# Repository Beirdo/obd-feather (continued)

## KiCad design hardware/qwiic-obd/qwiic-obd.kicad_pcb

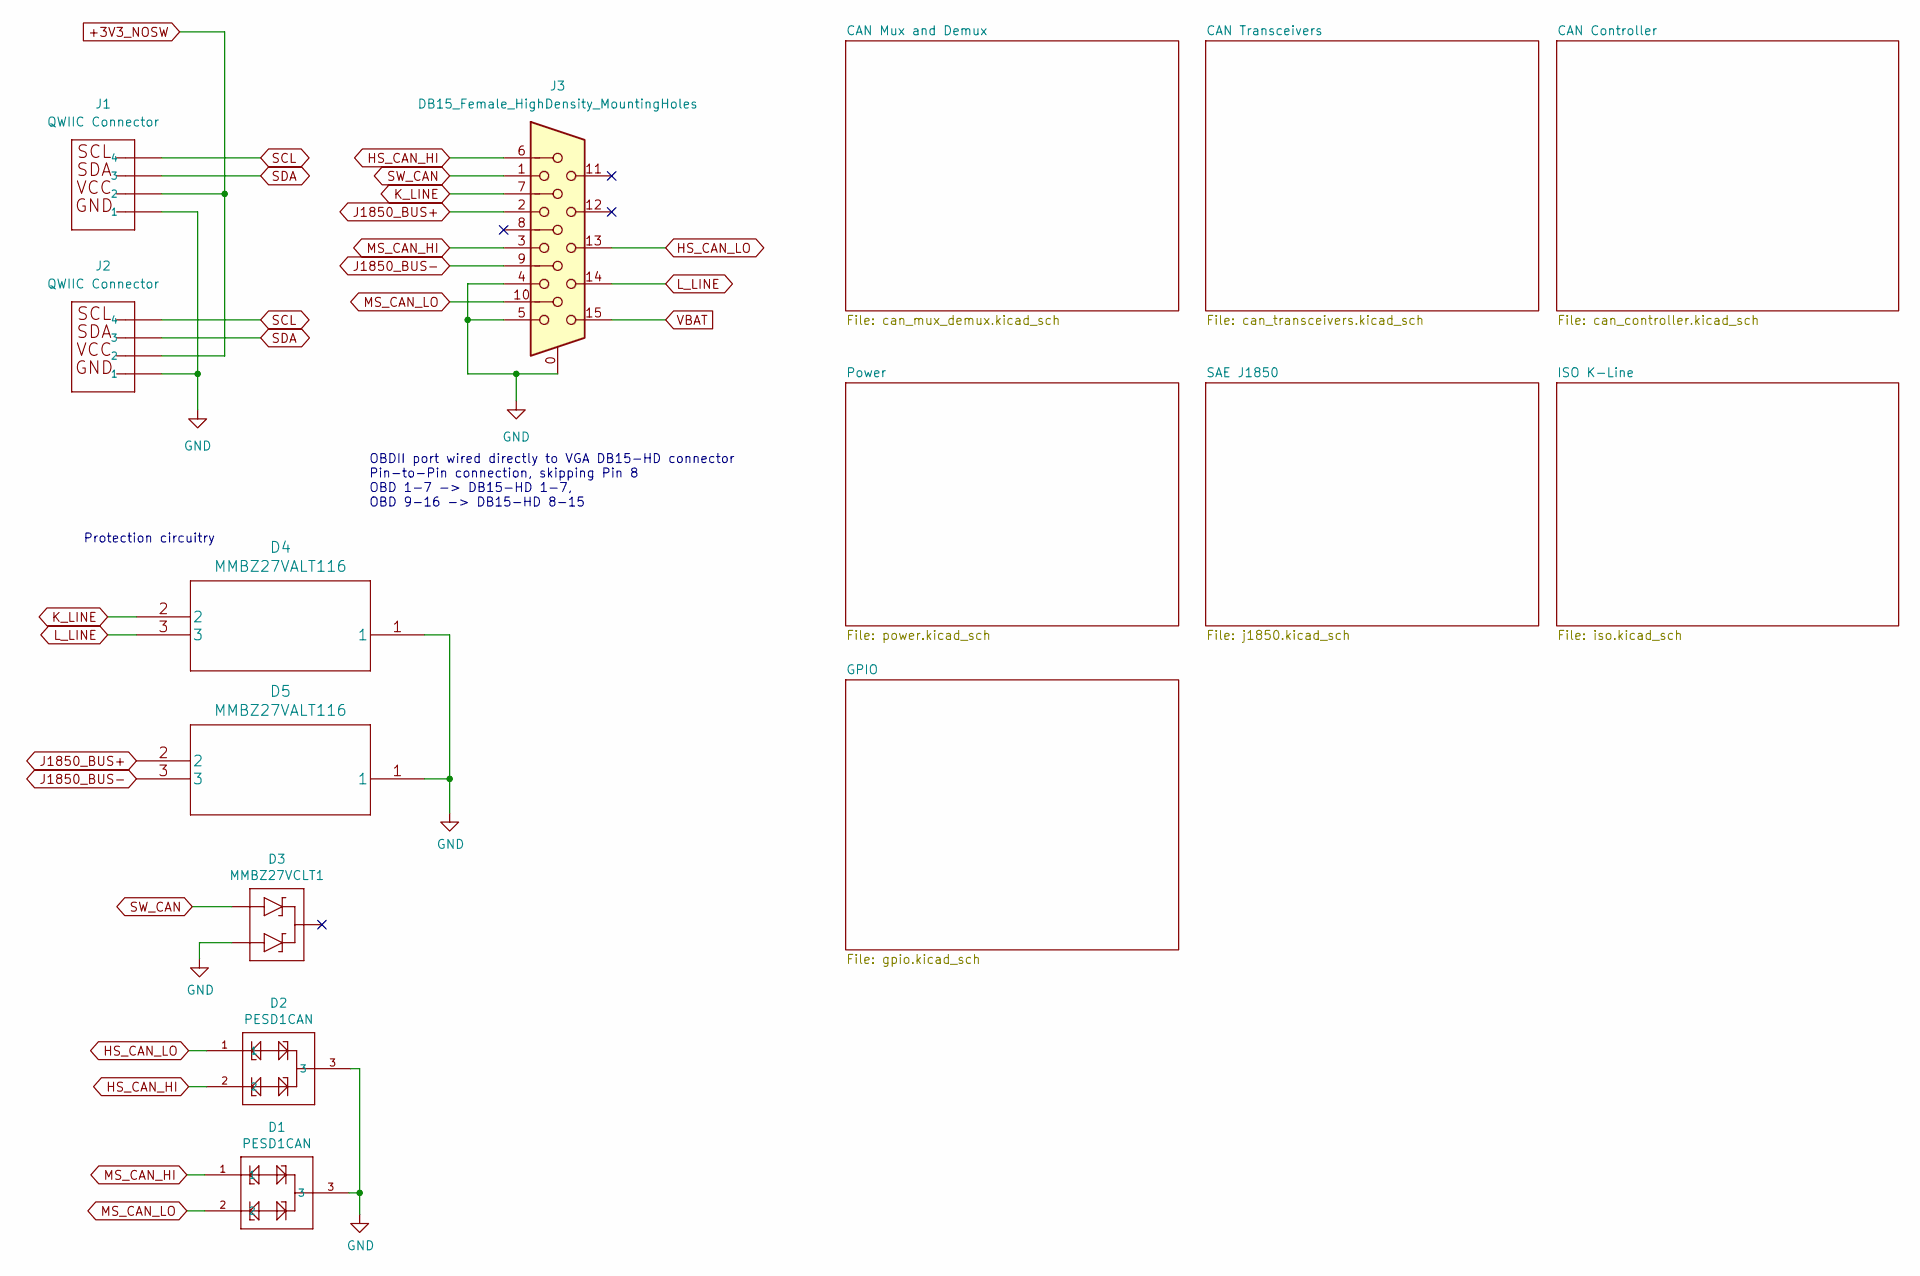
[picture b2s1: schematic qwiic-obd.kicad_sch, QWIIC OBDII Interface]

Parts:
D1, D2: PESD1CAN; SOT23-3; Digikey 1727-3817-1-ND
D3: MMBZ27VCLT1; SOT23-3; Digikey MMBZ27VCL-FDICT-ND
D4, D5: MMBZ27VALT116; SOT23-3; Digikey MMBZ27VALT116CT-ND
J1, J2: QWIIC Connector
J3: DB15_Female_HighDensity_MountingHoles; DSUB-15-HD_Female_Horizontal_P2.29x1.98mm_EdgePinOffset8.35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; Digikey L77HDE15SD1CH4FVGA-ND

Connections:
+3V3_NOSW: J1.2, J2.2; also elsewhere on the board
GND: D1.3, D2.3, D3.2 (A2), D4.1, D5.1, J1.1, J2.1, J3.0, J3.4, J3.5; also elsewhere on the board
HS_CAN_HI: D2.2, J3.6; also elsewhere on the board
HS_CAN_LO: D2.1, J3.13; also elsewhere on the board
J1850_BUS+: D5.2, J3.2; also elsewhere on the board
J1850_BUS-: D5.3, J3.9; also elsewhere on the board
K_LINE: D4.2, J3.7; also elsewhere on the board
L_LINE: D4.3, J3.14; also elsewhere on the board
MS_CAN_HI: D1.1, J3.3; also elsewhere on the board
MS_CAN_LO: D1.2, J3.10; also elsewhere on the board
SCL: J1.4, J2.4; also elsewhere on the board
SDA: J1.3, J2.3; also elsewhere on the board
SW_CAN: D3.1 (A1), J3.1; also elsewhere on the board
VBAT: J3.15; also elsewhere on the board

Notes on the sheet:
OBDII port wired directly to VGA DB15-HD connector Pin-to-Pin connection, skipping Pin 8 OBD 1-7 -> DB15-HD 1-7, OBD 9-16 -> DB15-HD 8-15
Protection circuitry

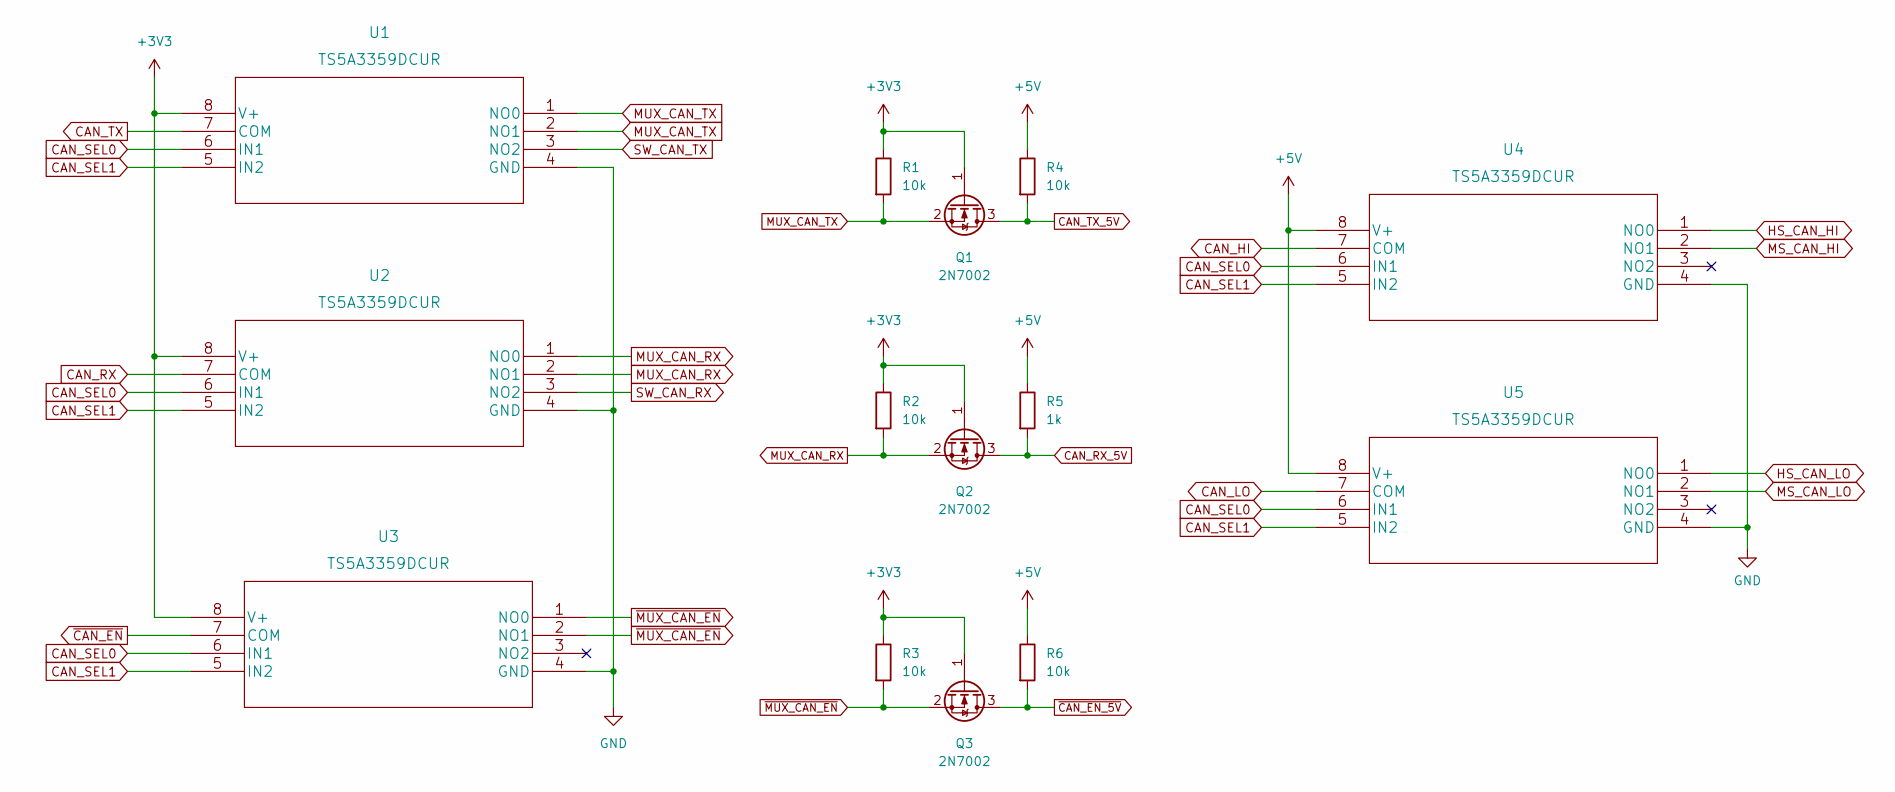
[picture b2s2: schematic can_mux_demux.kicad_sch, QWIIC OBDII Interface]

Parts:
Q1, Q2, Q3: 2N7002; SOT-23
R1, R2, R3, R4, R6: 10k; R_0805_2012Metric_Pad1.20x1.40mm_HandSolder
R5: 1k; R_0805_2012Metric_Pad1.20x1.40mm_HandSolder
U1, U2, U3, U4, U5: TS5A3359DCUR; Digikey 296-21193-1-ND

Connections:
+3V3: Q1.1 (G), Q2.1 (G), Q3.1 (G), R1.1, R2.1, R3.1, U1.8 (V+), U2.8 (V+), U3.8 (V+); also elsewhere on the board
+5V: R4.1, R5.1, R6.1, U4.8 (V+), U5.8 (V+); also elsewhere on the board
CAN_HI: U4.7 (COM); also elsewhere on the board
CAN_LO: U5.7 (COM); also elsewhere on the board
CAN_RX: U2.7 (COM); also elsewhere on the board
CAN_RX_5V: Q2.3 (D), R5.2; also elsewhere on the board
CAN_SEL0: U1.6 (IN1), U2.6 (IN1), U3.6 (IN1), U4.6 (IN1), U5.6 (IN1); also elsewhere on the board
CAN_SEL1: U1.5 (IN2), U2.5 (IN2), U3.5 (IN2), U4.5 (IN2), U5.5 (IN2); also elsewhere on the board
CAN_TX: U1.7 (COM); also elsewhere on the board
CAN_TX_5V: Q1.3 (D), R4.2; also elsewhere on the board
GND: U1.4 (GND), U2.4 (GND), U3.4 (GND), U4.4 (GND), U5.4 (GND); also elsewhere on the board
HS_CAN_HI: U4.1 (NO0); also elsewhere on the board
HS_CAN_LO: U5.1 (NO0); also elsewhere on the board
MS_CAN_HI: U4.2 (NO1); also elsewhere on the board
MS_CAN_LO: U5.2 (NO1); also elsewhere on the board
MUX_CAN_RX: Q2.2 (S), R2.2, U2.1 (NO0), U2.2 (NO1)
MUX_CAN_TX: Q1.2 (S), R1.2, U1.1 (NO0), U1.2 (NO1)
SW_CAN_RX: U2.3 (NO2); also elsewhere on the board
SW_CAN_TX: U1.3 (NO2); also elsewhere on the board
~CAN_EN_5V: Q3.3 (D), R6.2; also elsewhere on the board
~CAN_EN: U3.7 (COM)
~MUX_CAN_EN: Q3.2 (S), R3.2, U3.1 (NO0), U3.2 (NO1)

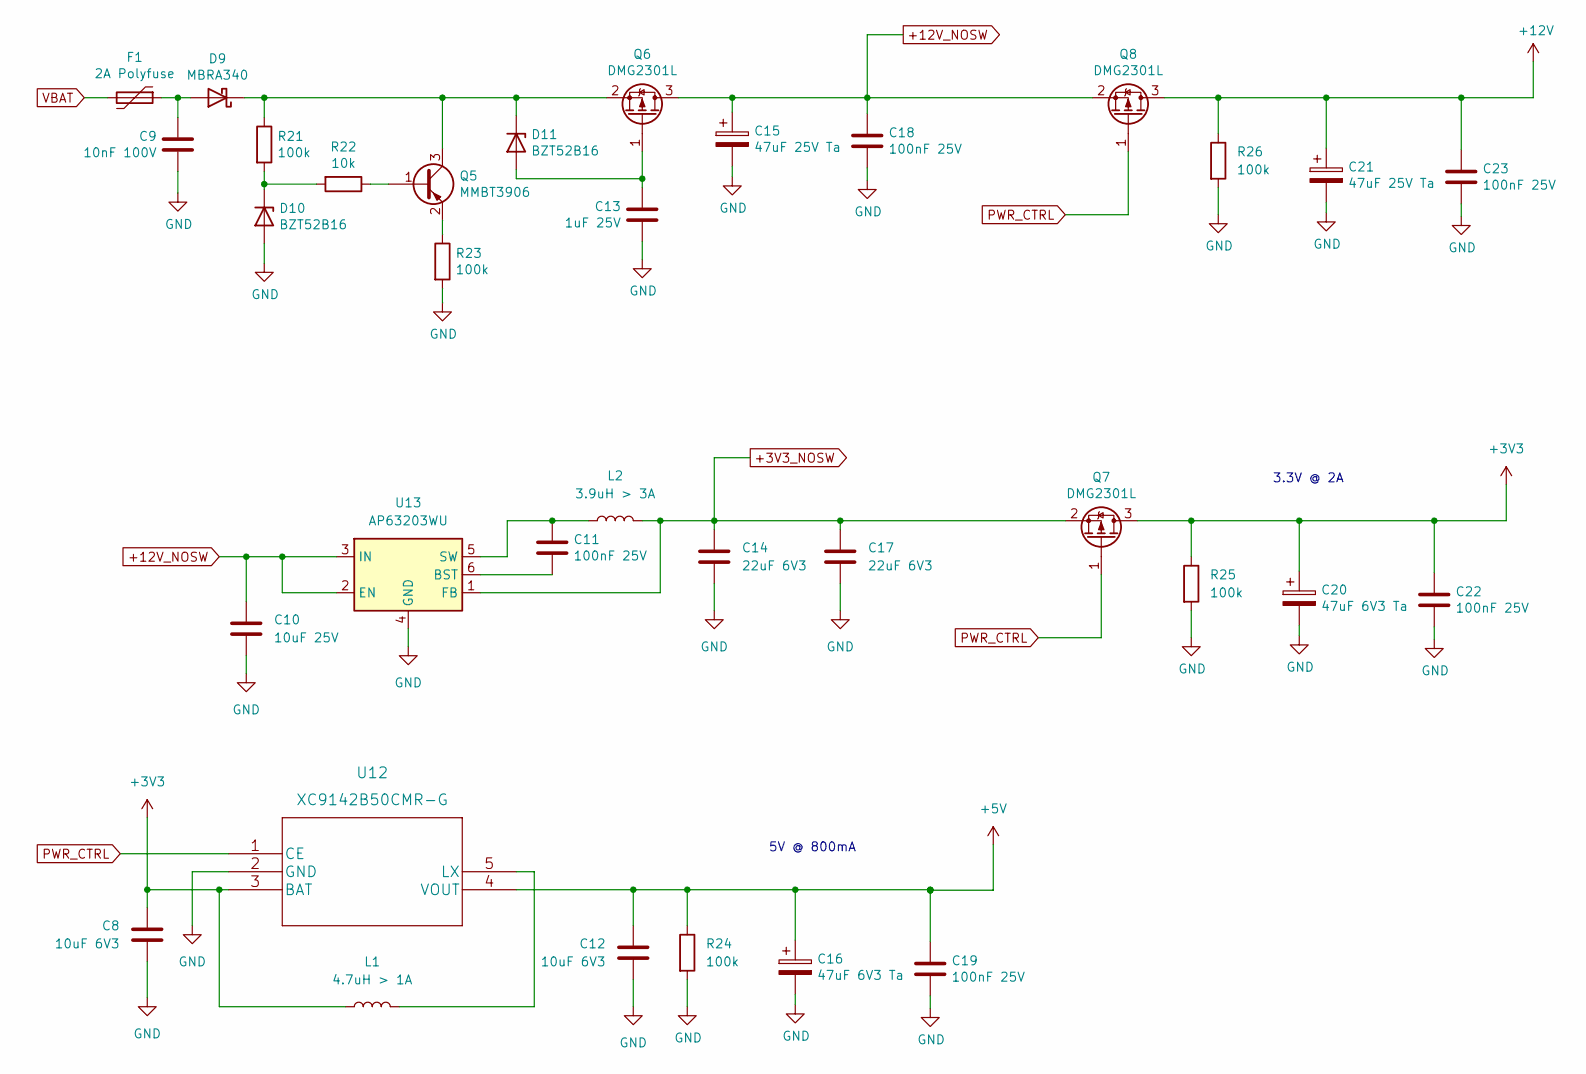
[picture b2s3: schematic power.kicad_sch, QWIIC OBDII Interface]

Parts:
C8, C12: 10uF 6V3; C_0805_2012Metric_Pad1.18x1.45mm_HandSolder
C9: 10nF 100V; C_0805_2012Metric_Pad1.18x1.45mm_HandSolder
C10: 10uF 25V; C_0805_2012Metric_Pad1.18x1.45mm_HandSolder
C11, C18, C19, C22, C23: 100nF 25V; C_0805_2012Metric_Pad1.18x1.45mm_HandSolder
C13: 1uF 25V; C_0805_2012Metric_Pad1.18x1.45mm_HandSolder
C14, C17: 22uF 6V3; C_0805_2012Metric_Pad1.18x1.45mm_HandSolder
C15, C21: 47uF 25V Ta; CP_EIA-7343-31_Kemet-D_Pad2.25x2.55mm_HandSolder
C16, C20: 47uF 6V3 Ta; CP_EIA-7343-31_Kemet-D_Pad2.25x2.55mm_HandSolder
D9: MBRA340; D_SMA
D10, D11: BZT52B16; D_SOD-123
F1: 2A Polyfuse; R_0805_2012Metric_Pad1.20x1.40mm_HandSolder
L1: 4.7uH > 1A; L_0603_1608Metric_Pad1.05x0.95mm_HandSolder
L2: 3.9uH > 3A; L_0603_1608Metric_Pad1.05x0.95mm_HandSolder
Q5: MMBT3906; SOT-23
Q6, Q7, Q8: DMG2301L; SOT-23
R21, R23, R24, R25, R26: 100k; R_0805_2012Metric_Pad1.20x1.40mm_HandSolder
R22: 10k; R_0805_2012Metric_Pad1.20x1.40mm_HandSolder
U12: XC9142B50CMR-G
U13: AP63203WU; TSOT-23-6

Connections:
+3V3: C8.2, C20.1, C22.1, L1.1, Q7.3 (D), R25.1, U12.3 (BAT); also elsewhere on the board
+3V3_NOSW: C14.1, C17.1, L2.2, Q7.2 (S), U13.1 (FB); also elsewhere on the board
+5V: C12.2, C16.1, C19.1, R24.1, U12.4 (VOUT); also elsewhere on the board
+12V: C21.1, C23.1, Q8.3 (D), R26.1; also elsewhere on the board
+12V_NOSW: C10.1, C15.1, C18.1, Q6.3 (D), Q8.2 (S), U13.2 (EN), U13.3 (IN)
GND: C8.1, C9.1, C10.2, C12.1, C13.1, C14.2, C15.2, C16.2, C17.2, C18.2, C19.2, C20.2, C21.2, C22.2, C23.2, D10.2 (A), R23.2, R24.2, R25.2, R26.2, U12.2 (GND), U13.4 (GND); also elsewhere on the board
unnamed: C9.2, D9.2 (A), F1.1
unnamed: C11.1, L2.1, U13.5 (SW)
unnamed: C11.2, U13.6 (BST)
unnamed: C13.2, D11.2 (A), Q6.1 (G)
unnamed: D9.1 (K), D11.1 (K), Q5.3 (C), Q6.2 (S), R21.1
unnamed: D10.1 (K), R21.2, R22.2
unnamed: L1.2, U12.5 (LX)
unnamed: Q5.1 (B), R22.1
unnamed: Q5.2 (E), R23.1
PWR_CTRL: Q7.1 (G), Q8.1 (G), U12.1 (CE); also elsewhere on the board
VBAT: F1.2; also elsewhere on the board

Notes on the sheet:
3.3V @ 2A
5V @ 800mA

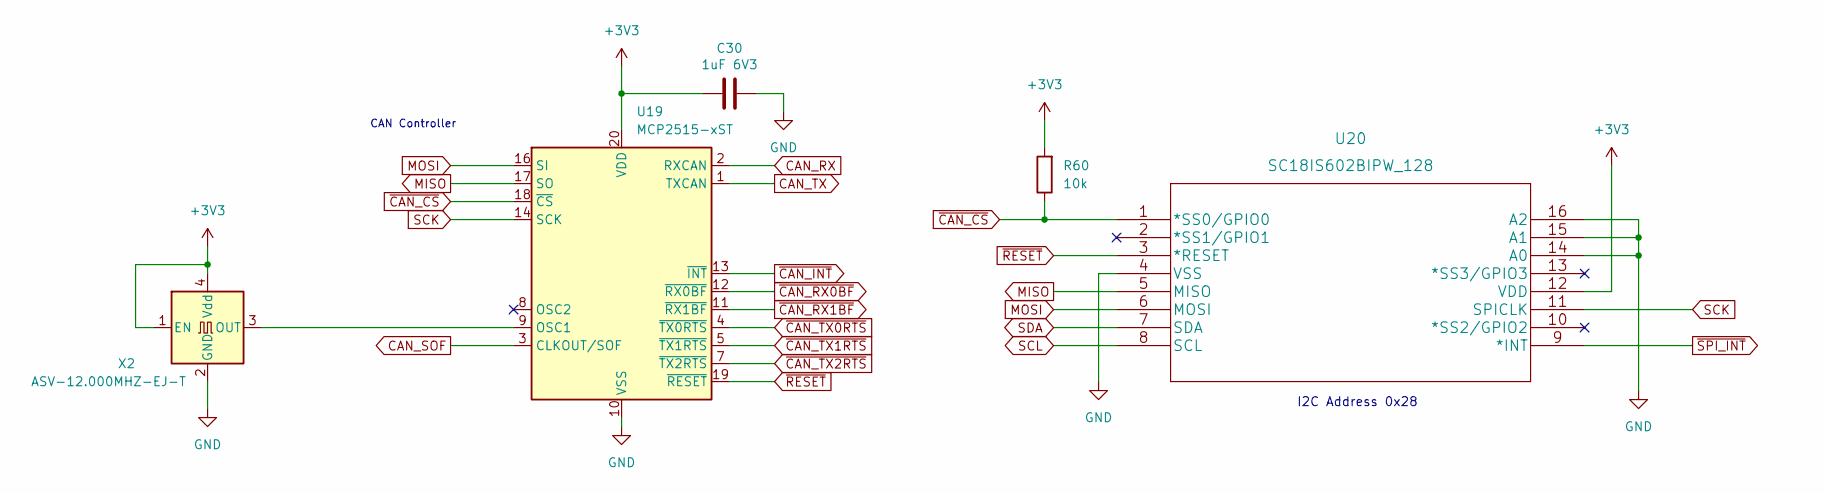
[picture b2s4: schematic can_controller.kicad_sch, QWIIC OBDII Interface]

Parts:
C30: 1uF 6V3; C_0805_2012Metric_Pad1.18x1.45mm_HandSolder
R60: 10k; R_0805_2012Metric_Pad1.20x1.40mm_HandSolder
U19: MCP2515-xST; TSSOP-20_4.4x6.5mm_P0.65mm
U20: SC18IS602BIPW_128
X2: ASV-12.000MHZ-EJ-T; Oscillator_SMD_Abracon_ASV-4Pin_7.0x5.1mm; Digikey 535-9309-1-ND

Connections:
+3V3: C30.2, R60.2, U19.20 (VDD), U20.12 (VDD), X2.1 (EN), X2.4 (Vdd); also elsewhere on the board
CAN_RX: U19.2 (RXCAN); also elsewhere on the board
CAN_SOF: U19.3 (CLKOUT/SOF); also elsewhere on the board
CAN_TX: U19.1 (TXCAN); also elsewhere on the board
GND: C30.1, U19.10 (VSS), U20.4 (VSS), U20.14 (A0), U20.15 (A1), U20.16 (A2), X2.2 (GND); also elsewhere on the board
MISO: U19.17 (SO), U20.5 (MISO)
MOSI: U19.16 (SI), U20.6 (MOSI)
unnamed: U19.9 (OSC1), X2.3 (OUT)
SCK: U19.14 (SCK), U20.11 (SPICLK)
SCL: U20.8 (SCL); also elsewhere on the board
SDA: U20.7 (SDA); also elsewhere on the board
~CAN_CS: R60.1, U19.18 (~CS), U20.1 (*SS0/GPIO0)
~CAN_INT: U19.13 (~INT); also elsewhere on the board
~CAN_RX0BF: U19.12 (~RX0BF); also elsewhere on the board
~CAN_RX1BF: U19.11 (~RX1BF); also elsewhere on the board
~CAN_TX0RTS: U19.4 (~TX0RTS); also elsewhere on the board
~CAN_TX1RTS: U19.5 (~TX1RTS); also elsewhere on the board
~CAN_TX2RTS: U19.7 (~TX2RTS); also elsewhere on the board
~RESET: U19.19 (~RESET), U20.3 (*RESET); also elsewhere on the board
~SPI_INT: U20.9 (*INT); also elsewhere on the board

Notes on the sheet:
CAN Controller
I2C Address 0x28

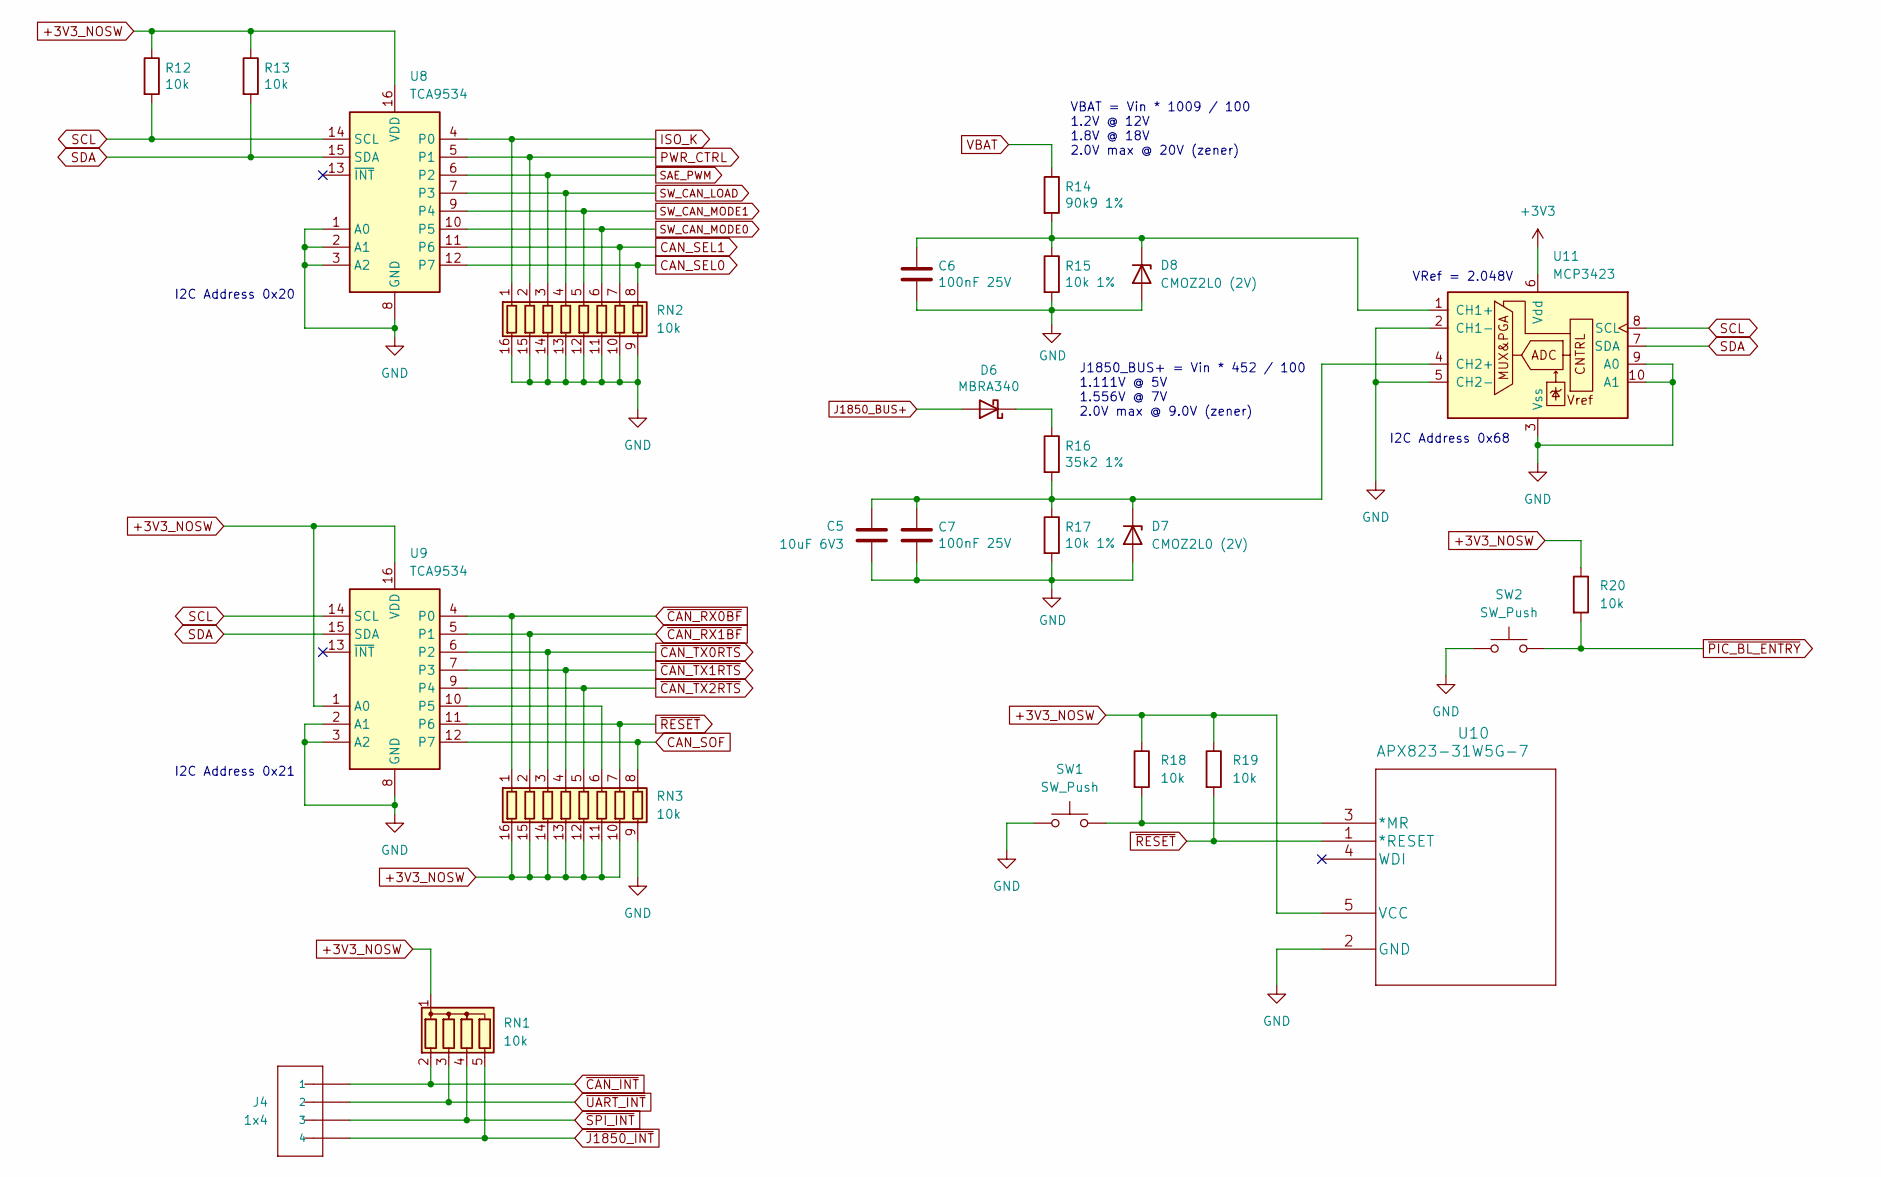
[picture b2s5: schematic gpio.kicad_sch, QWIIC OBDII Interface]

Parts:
C5: 10uF 6V3; C_0805_2012Metric_Pad1.18x1.45mm_HandSolder
C6, C7: 100nF 25V; C_0805_2012Metric_Pad1.18x1.45mm_HandSolder
D6: MBRA340; D_SMA
D7, D8: CMOZ2L0 (2V); D_SOD-523
J4: 1x4; PinSocket_1x04_P2.54mm_Vertical
R12, R13, R18, R19, R20: 10k; R_0805_2012Metric_Pad1.20x1.40mm_HandSolder
R14: 90k9 1%; R_0805_2012Metric_Pad1.20x1.40mm_HandSolder
R15, R17: 10k 1%; R_0805_2012Metric_Pad1.20x1.40mm_HandSolder
R16: 35k2 1%; R_0805_2012Metric_Pad1.20x1.40mm_HandSolder
RN1: 10k; R_Array_SIP5
RN2, RN3: 10k; 742C163103JP
SW1, SW2: SW_Push; SW_PUSH_6mm
U8, U9: TCA9534; TSSOP-16_4.4x5mm_P0.65mm
U10: APX823-31W5G-7; ADM6320BX33ARJZ-R7
U11: MCP3423; MSOP-10_3x3mm_P0.5mm

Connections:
+3V3: U11.6 (Vdd); also elsewhere on the board
+3V3_NOSW: R12.1, R13.1, R18.1, R19.1, R20.1, RN1.1 (common), RN3.10 (R7.2), RN3.11 (R6.2), RN3.12 (R5.2), RN3.13 (R4.2), RN3.14 (R3.2), RN3.15 (R2.2), RN3.16 (R1.2), U8.16 (VDD), U9.1 (A0), U9.16 (VDD), U10.5 (VCC); also elsewhere on the board
CAN_SEL0: RN2.8 (R8.1), U8.12 (P7); also elsewhere on the board
CAN_SEL1: RN2.7 (R7.1), U8.11 (P6); also elsewhere on the board
CAN_SOF: RN3.8 (R8.1), U9.12 (P7); also elsewhere on the board
GND: C5.1, C6.2, C7.2, D7.2 (A), D8.2 (A), R15.2, R17.2, RN2.9 (R8.2), RN2.10 (R7.2), RN2.11 (R6.2), RN2.12 (R5.2), RN2.13 (R4.2), RN2.14 (R3.2), RN2.15 (R2.2), RN2.16 (R1.2), RN3.9 (R8.2), SW1.1, SW2.1, U8.1 (A0), U8.2 (A1), U8.3 (A2), U8.8 (GND), U9.2 (A1), U9.3 (A2), U9.8 (GND), U10.2 (GND), U11.2 (CH1-), U11.3 (Vss), U11.5 (CH2-), U11.9 (A0), U11.10 (A1); also elsewhere on the board
ISO_K: RN2.1 (R1.1), U8.4 (P0); also elsewhere on the board
J1850_BUS+: D6.2 (A); also elsewhere on the board
unnamed: C5.2, C7.1, D7.1 (K), R16.2, R17.1, U11.4 (CH2+)
unnamed: C6.1, D8.1 (K), R14.2, R15.1, U11.1 (CH1+)
unnamed: D6.1 (K), R16.1
unnamed: R18.2, SW1.2, U10.3 (*MR)
unnamed: RN3.6 (R6.1), U9.10 (P5)
PWR_CTRL: RN2.2 (R2.1), U8.5 (P1); also elsewhere on the board
SAE_PWM: RN2.3 (R3.1), U8.6 (P2); also elsewhere on the board
SCL: R12.2, U8.14 (SCL), U9.14 (SCL), U11.8 (SCL); also elsewhere on the board
SDA: R13.2, U8.15 (SDA), U9.15 (SDA), U11.7 (SDA); also elsewhere on the board
SW_CAN_LOAD: RN2.4 (R4.1), U8.7 (P3); also elsewhere on the board
SW_CAN_MODE0: RN2.6 (R6.1), U8.10 (P5); also elsewhere on the board
SW_CAN_MODE1: RN2.5 (R5.1), U8.9 (P4); also elsewhere on the board
VBAT: R14.1; also elsewhere on the board
~CAN_INT: J4.1, RN1.2 (R1); also elsewhere on the board
~CAN_RX0BF: RN3.1 (R1.1), U9.4 (P0); also elsewhere on the board
~CAN_RX1BF: RN3.2 (R2.1), U9.5 (P1); also elsewhere on the board
~CAN_TX0RTS: RN3.3 (R3.1), U9.6 (P2); also elsewhere on the board
~CAN_TX1RTS: RN3.4 (R4.1), U9.7 (P3); also elsewhere on the board
~CAN_TX2RTS: RN3.5 (R5.1), U9.9 (P4); also elsewhere on the board
~J1850_INT: J4.4, RN1.5 (R4); also elsewhere on the board
~PIC_BL_ENTRY: R20.2, SW2.2
~RESET: R19.2, RN3.7 (R7.1), U9.11 (P6), U10.1 (*RESET); also elsewhere on the board
~SPI_INT: J4.3, RN1.4 (R3); also elsewhere on the board
~UART_INT: J4.2, RN1.3 (R2); also elsewhere on the board

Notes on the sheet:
J1850_BUS+ = Vin * 452 / 100 1.111V @ 5V 1.556V @ 7V 2.0V max @ 9.0V (zener)
I2C Address 0x68
I2C Address 0x21
VRef = 2.048V
I2C Address 0x20
VBAT = Vin * 1009 / 100 1.2V @ 12V 1.8V @ 18V 2.0V max @ 20V (zener)

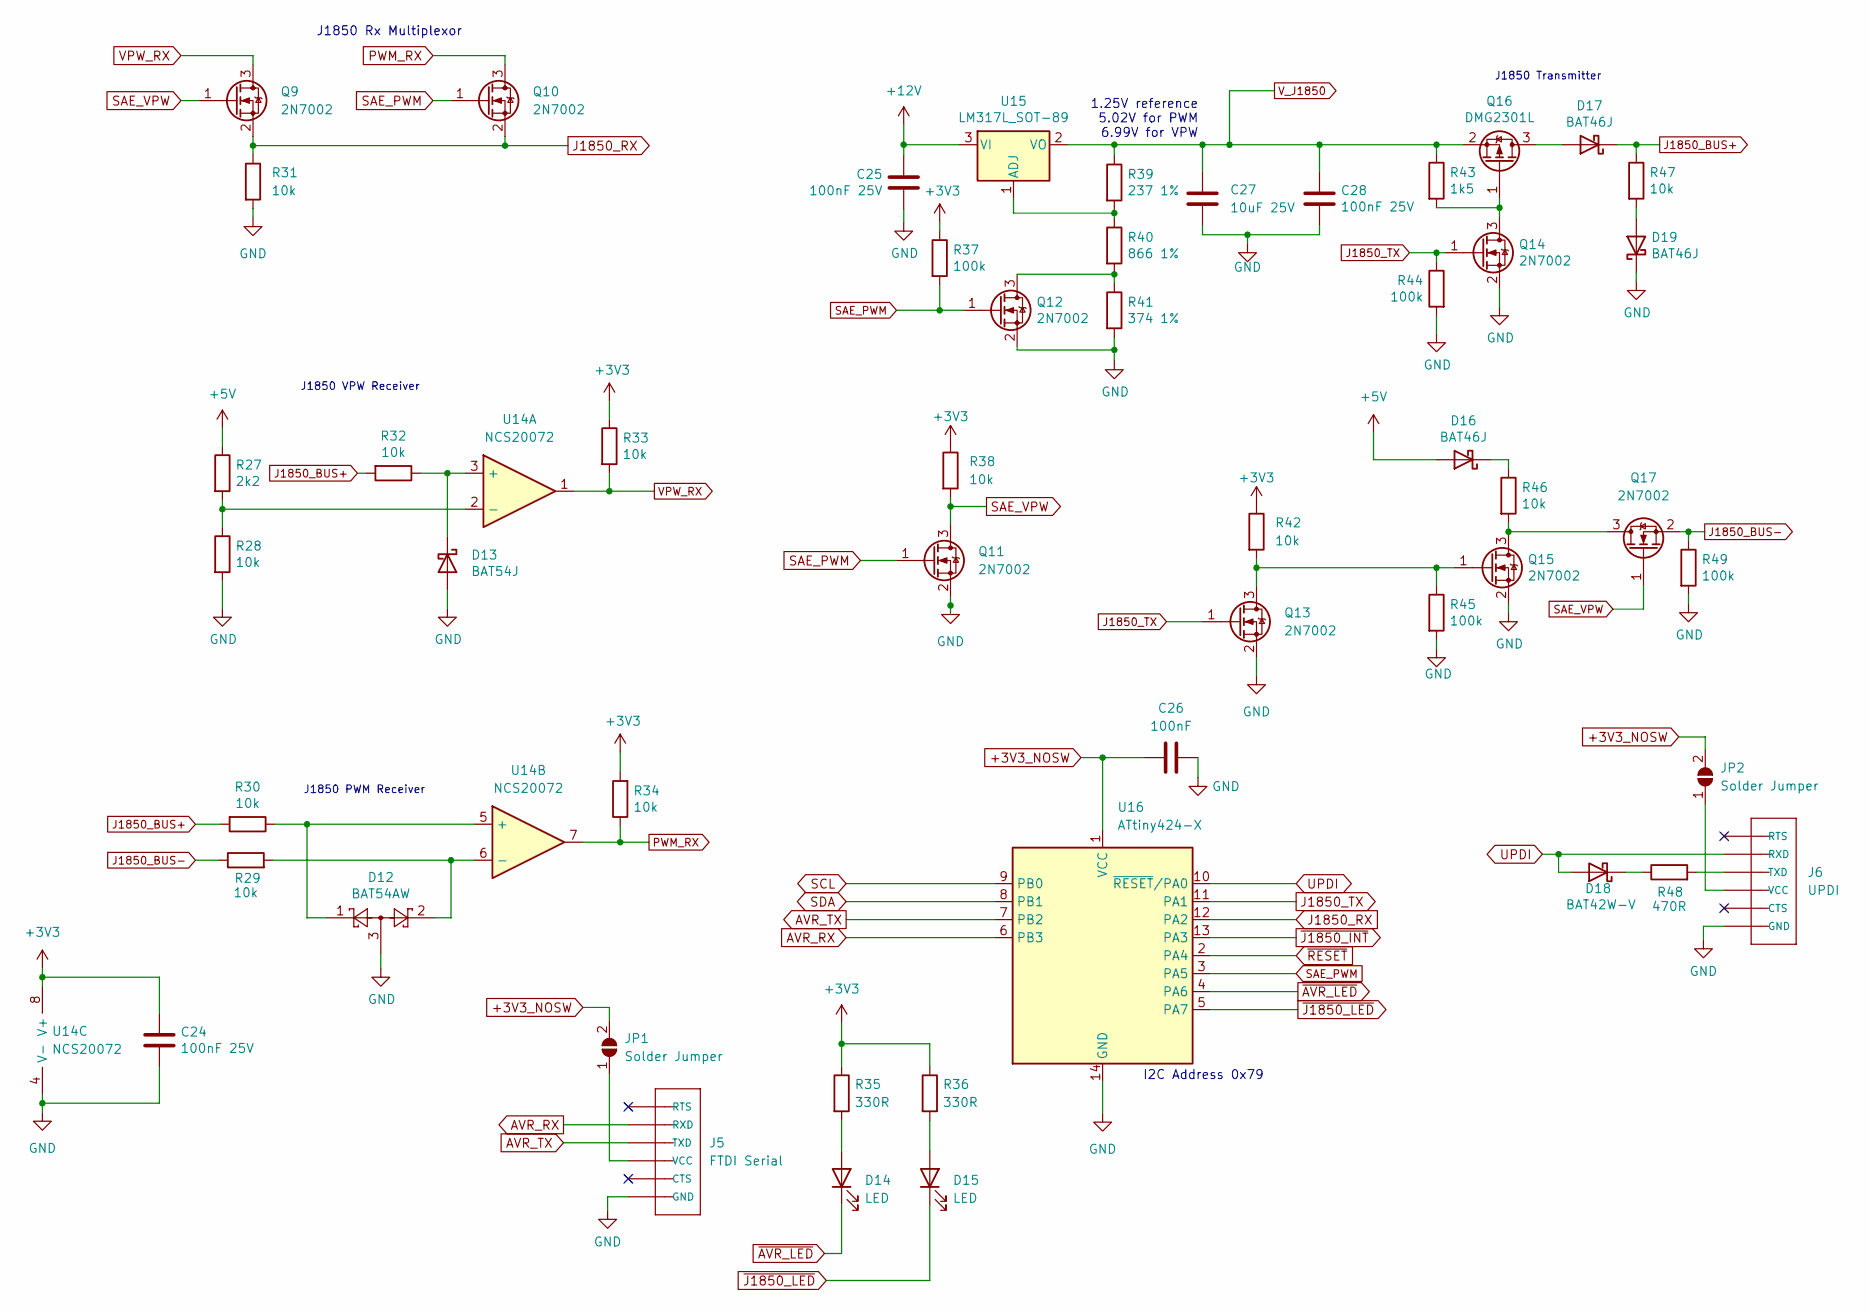
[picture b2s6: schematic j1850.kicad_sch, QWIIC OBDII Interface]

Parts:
C24, C25, C28: 100nF 25V; C_0805_2012Metric_Pad1.18x1.45mm_HandSolder
C26: 100nF; C_0805_2012Metric_Pad1.18x1.45mm_HandSolder
C27: 10uF 25V; C_0805_2012Metric_Pad1.18x1.45mm_HandSolder
D12: BAT54AW; SOT-323_SC-70
D13: BAT54J; D_SOD-123
D14, D15: LED; LED_0805_2012Metric_Pad1.15x1.40mm_HandSolder
D16, D17, D19: BAT46J; D_SOD-123
D18: BAT42W-V; D_SOD-123
J5: FTDI Serial; FTDI_BASIC
J6: UPDI; FTDI_BASIC
JP1, JP2: Solder Jumper; SolderJumper-2_P1.3mm_Open_TrianglePad1.0x1.5mm
Q9, Q10, Q11, Q12, Q13, Q14, Q15, Q17: 2N7002; SOT-23
Q16: DMG2301L; SOT-23
R27: 2k2; R_0805_2012Metric_Pad1.20x1.40mm_HandSolder
R28, R29, R30, R31, R32, R33, R34, R38, R42, R46, R47: 10k; R_0805_2012Metric_Pad1.20x1.40mm_HandSolder
R35, R36: 330R; R_0805_2012Metric_Pad1.20x1.40mm_HandSolder
R37, R44, R45, R49: 100k; R_0805_2012Metric_Pad1.20x1.40mm_HandSolder
R39: 237 1%; R_0805_2012Metric_Pad1.20x1.40mm_HandSolder
R40: 866 1%; R_0805_2012Metric_Pad1.20x1.40mm_HandSolder
R41: 374 1%; R_0805_2012Metric_Pad1.20x1.40mm_HandSolder
R43: 1k5; R_0805_2012Metric_Pad1.20x1.40mm_HandSolder
R48: 470R; R_0805_2012Metric_Pad1.20x1.40mm_HandSolder
U14: NCS20072; TSSOP-8_4.4x3mm_P0.65mm
U15: LM317L_SOT-89; SOT-89-3
U16: ATtiny424-X; TSSOP-14_4.4x5mm_P0.65mm

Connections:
+3V3: C24.2, R33.1, R34.2, R35.1, R36.1, R37.1, R38.1, R42.1, U14.8 (V+); also elsewhere on the board
+3V3_NOSW: C26.2, JP1.2 (B), JP2.2 (B), U16.1 (VCC); also elsewhere on the board
+5V: D16.2 (A), R27.1; also elsewhere on the board
+12V: C25.2, U15.3 (VI); also elsewhere on the board
AVR_RX: J5.5 (RXD), U16.6 (PB3)
AVR_TX: J5.4 (TXD), U16.7 (PB2)
GND: C24.1, C25.1, C26.1, C27.2, C28.2, D12.3, D13.2 (A), D19.1 (K), J5.1 (GND), J6.1 (GND), Q11.2 (S), Q12.2 (S), Q13.2 (S), Q14.2 (S), Q15.2 (S), R28.2, R31.2, R41.2, R44.2, R45.2, R49.2, U14.4 (V-), U16.14 (GND); also elsewhere on the board
J1850_BUS+: D17.1 (K), R30.2, R32.2, R47.1; also elsewhere on the board
J1850_BUS-: Q17.2 (S), R29.1, R49.1; also elsewhere on the board
J1850_RX: Q9.2 (S), Q10.2 (S), R31.1, U16.12 (PA2)
J1850_TX: Q13.1 (G), Q14.1 (G), R44.1, U16.11 (PA1)
unnamed: D12.1, R30.1, U14.5 (+)
unnamed: D12.2, R29.2, U14.6 (-)
unnamed: D13.1 (K), R32.1, U14.3 (+)
unnamed: D14.2 (A), R35.2
unnamed: D15.2 (A), R36.2
unnamed: D16.1 (K), R46.1
unnamed: D17.2 (A), Q16.3 (D)
unnamed: D18.1 (K), R48.1
unnamed: D19.2 (A), R47.2
unnamed: J5.3 (VCC), JP1.1 (A)
unnamed: J6.3 (VCC), JP2.1 (A)
unnamed: Q12.3 (D), R40.2, R41.1
unnamed: Q13.3 (D), Q15.1 (G), R42.2, R45.1
unnamed: Q14.3 (D), Q16.1 (G), R43.2
unnamed: Q15.3 (D), Q17.3 (D), R46.2
unnamed: R27.2, R28.1, U14.2 (-)
unnamed: R39.2, R40.1, U15.1 (ADJ)
unnamed: J6.4 (TXD), R48.2
PWM_RX: Q10.3 (D), R34.1, U14.7
SAE_PWM: Q10.1 (G), Q11.1 (G), Q12.1 (G), R37.2, U16.3 (PA5); also elsewhere on the board
SAE_VPW: Q9.1 (G), Q11.3 (D), Q17.1 (G), R38.2
SCL: U16.9 (PB0); also elsewhere on the board
SDA: U16.8 (PB1); also elsewhere on the board
UPDI: D18.2 (A), J6.5 (RXD), U16.10 (~RESET/PA0)
VPW_RX: Q9.3 (D), R33.2, U14.1
V_J1850: C27.1, C28.1, Q16.2 (S), R39.1, R43.1, U15.2 (VO)
~AVR_LED: D14.1 (K), U16.4 (PA6)
~J1850_INT: U16.13 (PA3); also elsewhere on the board
~J1850_LED: D15.1 (K), U16.5 (PA7)
~RESET: U16.2 (PA4); also elsewhere on the board

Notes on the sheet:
J1850 Transmitter
J1850 Rx Multiplexor
J1850 VPW Receiver
I2C Address 0x79
J1850 PWM Receiver
1.25V reference 5.02V for PWM 6.99V for VPW

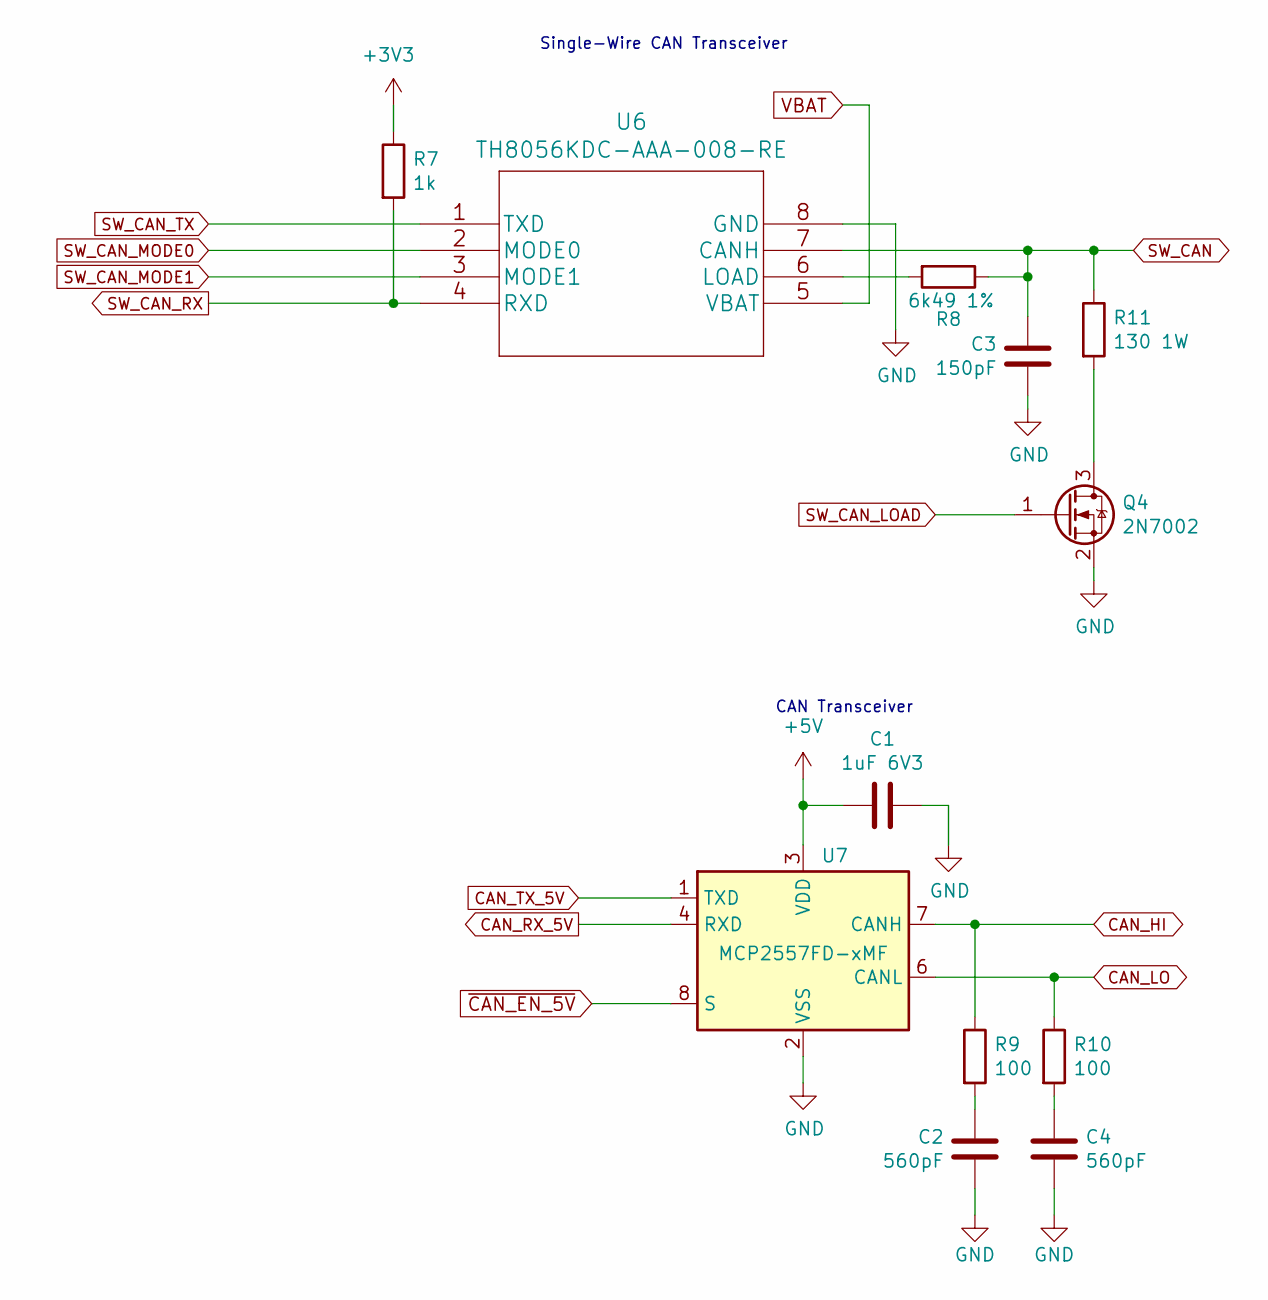
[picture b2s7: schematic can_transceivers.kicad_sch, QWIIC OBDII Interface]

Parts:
C1: 1uF 6V3; C_0805_2012Metric_Pad1.18x1.45mm_HandSolder
C2, C4: 560pF; C_0805_2012Metric_Pad1.18x1.45mm_HandSolder
C3: 150pF; C_0805_2012Metric_Pad1.18x1.45mm_HandSolder
Q4: 2N7002; SOT-23
R7: 1k; R_0805_2012Metric_Pad1.20x1.40mm_HandSolder
R8: 6k49 1%; R_0805_2012Metric_Pad1.20x1.40mm_HandSolder
R9, R10: 100; R_0805_2012Metric_Pad1.20x1.40mm_HandSolder
R11: 130 1W; R_2512_6332Metric_Pad1.40x3.35mm_HandSolder
U6: TH8056KDC-AAA-008-RE
U7: MCP2557FD-xMF; DFN-8-1EP_3x3mm_P0.65mm_EP1.55x2.4mm

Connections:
+3V3: R7.1; also elsewhere on the board
+5V: C1.2, U7.3 (VDD); also elsewhere on the board
CAN_HI: R9.1, U7.7 (CANH); also elsewhere on the board
CAN_LO: R10.1, U7.6 (CANL); also elsewhere on the board
CAN_RX_5V: U7.4 (RXD); also elsewhere on the board
CAN_TX_5V: U7.1 (TXD); also elsewhere on the board
GND: C1.1, C2.1, C3.1, C4.2, Q4.2 (S), U6.8 (GND), U7.2 (VSS), U7.9 (VSS); also elsewhere on the board
unnamed: C2.2, R9.2
unnamed: C4.1, R10.2
unnamed: Q4.3 (D), R11.2
unnamed: R8.2, U6.6 (LOAD)
SW_CAN: C3.2, R8.1, R11.1, U6.7 (CANH); also elsewhere on the board
SW_CAN_LOAD: Q4.1 (G); also elsewhere on the board
SW_CAN_MODE0: U6.2 (MODE0); also elsewhere on the board
SW_CAN_MODE1: U6.3 (MODE1); also elsewhere on the board
SW_CAN_RX: R7.2, U6.4 (RXD); also elsewhere on the board
SW_CAN_TX: U6.1 (TXD); also elsewhere on the board
VBAT: U6.5 (VBAT); also elsewhere on the board
~CAN_EN_5V: U7.8 (S); also elsewhere on the board

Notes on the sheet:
CAN Transceiver
Single-Wire CAN Transceiver
